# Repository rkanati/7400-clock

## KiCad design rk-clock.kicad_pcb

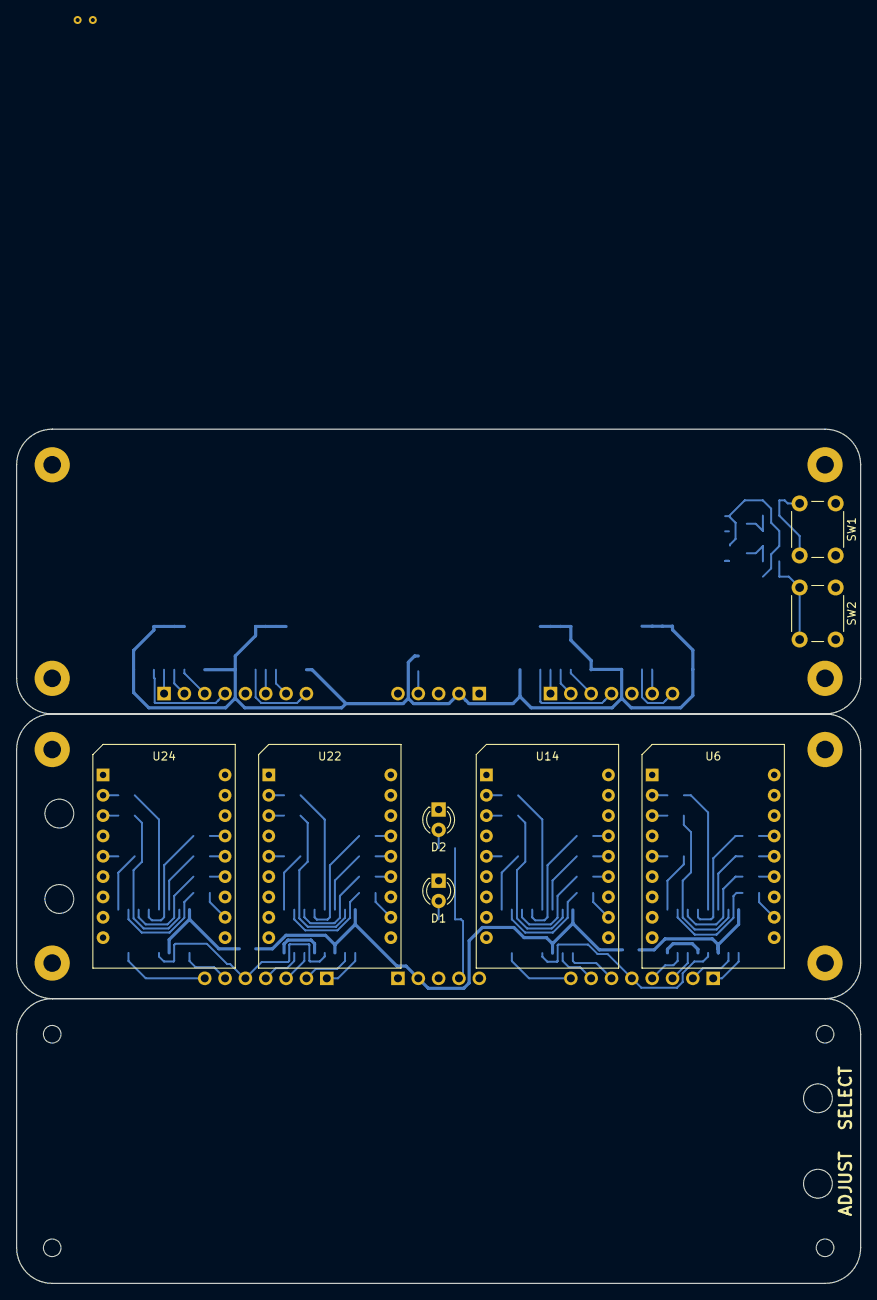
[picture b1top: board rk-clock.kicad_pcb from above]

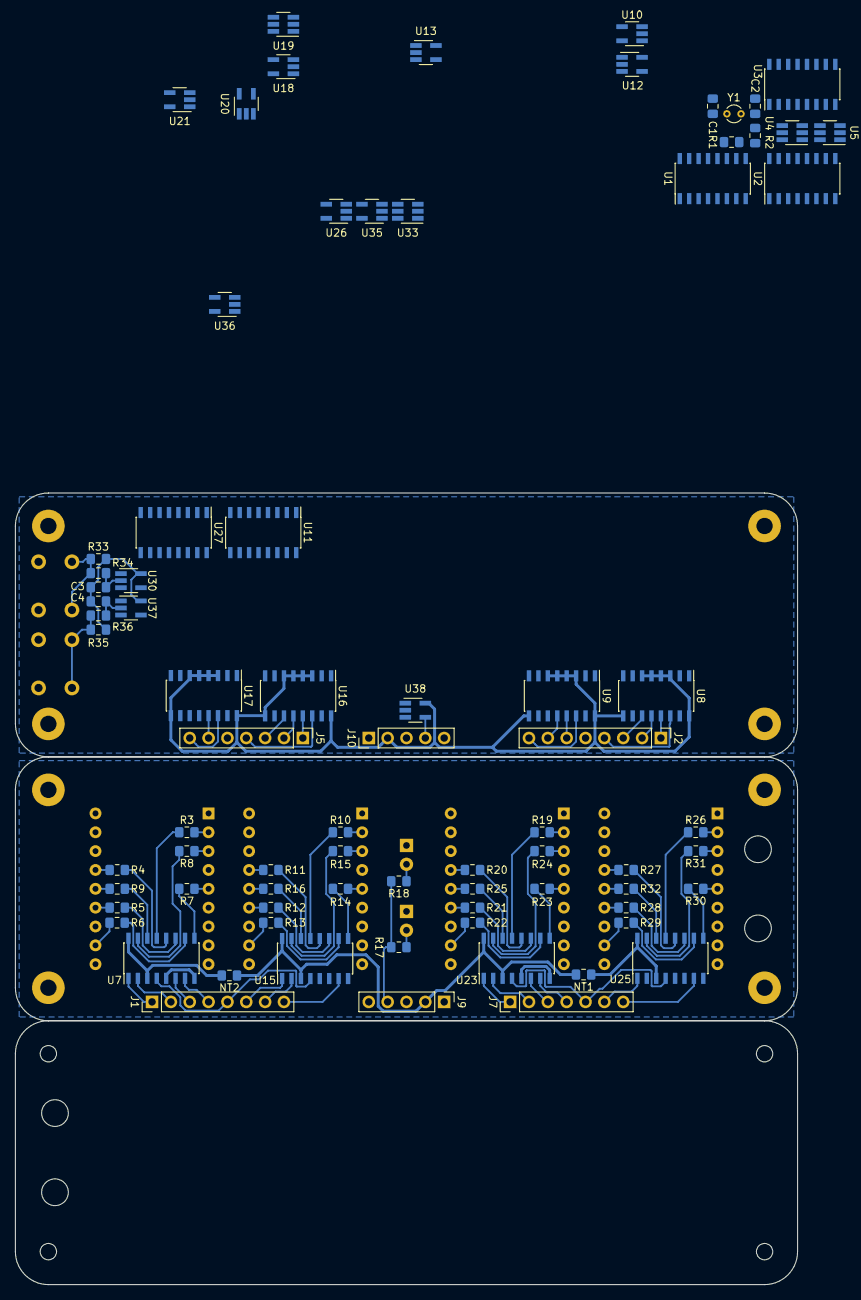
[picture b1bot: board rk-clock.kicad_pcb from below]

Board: 2 copper layers, 105.4 x 106.7 mm, 102 parts (78 on the bottom side), 132 nets.

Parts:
C1: 22p; C_0805_2012Metric_Pad1.15x1.40mm_HandSolder
C2: 100p; C_0805_2012Metric_Pad1.15x1.40mm_HandSolder
C3, C4: 1u; C_0805_2012Metric_Pad1.15x1.40mm_HandSolder
D1, D2: LED_Small; LED_D3.0mm
H1, H2, H3, H4, H9, H10, H11, H12: MountingHole_Pad; MountingHole_2.2mm_M2_Pad
H5, H6, H7, H8: MountingHole; MountingHole_2.2mm_M2
H13, H14, H15, H16: MountingHole; button-hole
J1: min_display; PinHeader_1x08_P2.54mm_Vertical
J2: min_control; PinHeader_1x08_P2.54mm_Vertical
J5: hour_control; PinHeader_1x07_P2.54mm_Vertical
J7: hour_display; PinHeader_1x07_P2.54mm_Vertical
J9: colon_display; PinHeader_1x05_P2.54mm_Vertical
J10: colon_control; PinHeader_1x05_P2.54mm_Vertical
NT1, NT2: Net-Tie_2; R_0805_2012Metric_Pad1.15x1.40mm_HandSolder
R1: 1M; R_0805_2012Metric_Pad1.15x1.40mm_HandSolder
R2: 2k2; R_0805_2012Metric_Pad1.15x1.40mm_HandSolder
R3, R4, R5, R6, R7, R8, R9, R10, R11, R12, R13, R14, R15, R16, R17, R18, R19, R20, R21, R22, R23, R24, R25, R26, R27, R28, R29, R30, R31, R32: 470; R_0805_2012Metric_Pad1.15x1.40mm_HandSolder
R33, R34, R35, R36: 47k; R_0805_2012Metric_Pad1.15x1.40mm_HandSolder
SW1: mode; SW_PUSH_6mm_H9.5mm
SW2: increase; SW_PUSH_6mm_H9.5mm
U1: '4060; SOIC-16_3.9x9.9mm_P1.27mm
U2, U3, U8, U9, U16, U17: '163; SOIC-16_3.9x9.9mm_P1.27mm
U4, U5, U33: '10; SOT-23-6_Handsoldering
U6, U14, U22, U24: LED-7Seg-18DIP; 7Seg-18DIP
U7, U15, U23, U25: '4511; SOIC-16_3.9x9.9mm_P1.27mm
U10, U13, U18, U26: '08; SOT-23-5_HandSoldering
U11: '158; SOIC-16_3.9x9.9mm_P1.27mm
U12, U21: '04; SOT-23-5_HandSoldering
U19: '11; SOT-23-6_Handsoldering
U20: '02; SOT-23-5_HandSoldering
U27: '175; SOIC-16_3.9x9.9mm_P1.27mm
U30, U37: '17; SOT-23-5_HandSoldering
U35, U36, U38: '32; SOT-23-5_HandSoldering
Y1: 32k768; Crystal_Round_D2.0mm_Vertical

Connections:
/2Hz_clk: U1.3, U2.2, U11.3
/DGND: D1.1, D2.1, H9.1, H10.1, H11.1, H12.1, J9.1, J9.3, J9.5, U6.4, U6.6, U6.9, U6.10, U6.12, U6.17, U7.5, U7.8, U14.4, U14.6, U14.9, U14.10, U14.12, U14.17, U15.5, U15.6, U15.8, U22.4, U22.6, U22.9, U22.10, U22.12, U22.17, U23.5, U23.8, U24.4, U24.6, U24.9, U24.10, U24.12, U24.17, U25.2, U25.5, U25.6, U25.8
/DVCC: J9.2, NT1.1, NT1.2, NT2.1, NT2.2, U7.3, U7.16, U15.3, U15.16, U23.3, U23.16, U25.3, U25.16
/colon_control: J10.4, U38.4
/count_clk: U8.2, U9.2, U11.4, U16.2, U17.2
/hour_bit0: J5.4, U16.14, U18.1, U19.1
/hour_bit1: J5.1, U16.13, U19.3
/hour_bit2: J5.2, U16.12
/hour_bit3: J5.3, U16.11, U18.2
/hour_en: U13.4, U16.7, U16.10
/min_bit0: J2.4, U8.14, U10.1
/min_bit1: J2.1, U8.13
/min_bit2: J2.2, U8.12
/min_bit3: J2.3, U8.11, U10.2
/min_en: U8.7, U8.10, U26.4
/tenhour_bit0: J5.7, U17.14
/tenhour_bit1: J5.6, U17.13, U19.6
/tenmin_bit0: J2.8, U9.14, U33.6
/tenmin_bit1: J2.6, U9.13
/tenmin_bit2: J2.7, U9.12, U33.1
/twosec_clk: U2.13, U4.1, U35.1, U36.1, U38.1
/~59_mins: U9.1, U11.14, U33.4
/~hour_blank: J5.5, U36.4
/~increase: U11.10, U37.4
/~min_blank: J2.5, U35.4
/~min_clk: U3.1, U5.4, U11.2
/~run: U11.1, U27.2, U38.2
/~set_hours: U11.13, U27.11, U36.2
/~set_mins: U11.6, U27.6, U35.2
GND: C1.2, C2.2, H1.1, H2.1, H3.1, H4.1, J10.1, J10.3, J10.5, SW1.1, SW2.1, U1.8, U1.12, U2.3, U2.4, U2.5, U2.6, U2.8, U3.3, U3.4, U3.5, U3.6, U3.8, U4.2, U5.2, U8.8, U9.8, U10.3, U11.5, U11.8, U11.11, U11.15, U12.3, U13.3, U16.8, U17.8, U18.3, U19.2, U20.3, U21.3, U26.3, U27.8, U30.3, U33.2, U35.3, U36.3, U37.3, U38.3
unnamed: C1.1, R1.2, U1.11, Y1.2
unnamed: C2.1, R2.2, Y1.1
unnamed: C3.2, R34.1, U30.2
unnamed: C4.2, R36.1, U37.2
unnamed: D1.2, R17.1
unnamed: D2.2, R18.1
unnamed: J1.1, U7.1
unnamed: J1.2, U7.2
unnamed: J1.3, U7.6
unnamed: J1.4, U7.7
unnamed: J1.5, U7.4, U15.4
unnamed: J1.6, U15.1
unnamed: J1.7, U15.2
unnamed: J1.8, U15.7
unnamed: J7.1, U23.1
unnamed: J7.2, U23.2
unnamed: J7.3, U23.6
unnamed: J7.4, U23.7
unnamed: J7.5, U23.4, U25.4
unnamed: J7.6, U25.1
unnamed: J7.7, U25.7
unnamed: J9.4, R17.2, R18.2
unnamed: R1.1, R2.1, U1.10
unnamed: R3.1, U6.2
unnamed: R3.2, U7.13
unnamed: R4.1, U6.15
unnamed: R4.2, U7.12
unnamed: R5.1, U6.13
unnamed: R5.2, U7.11
unnamed: R6.1, U6.11
unnamed: R6.2, U7.10
unnamed: R7.1, U6.5
unnamed: R7.2, U7.9
unnamed: R8.1, U6.3
unnamed: R8.2, U7.15
unnamed: R9.1, U6.14
unnamed: R9.2, U7.14
unnamed: R10.1, U14.2
unnamed: R10.2, U15.13
unnamed: R11.1, U14.15
unnamed: R11.2, U15.12
unnamed: R12.1, U14.13
unnamed: R12.2, U15.11
unnamed: R13.1, U14.11
unnamed: R13.2, U15.10
unnamed: R14.1, U14.5
unnamed: R14.2, U15.9
unnamed: R15.1, U14.3
unnamed: R15.2, U15.15
unnamed: R16.1, U14.14
unnamed: R16.2, U15.14
unnamed: R19.1, U22.2
unnamed: R19.2, U23.13
unnamed: R20.1, U22.15
unnamed: R20.2, U23.12
unnamed: R21.1, U22.13
unnamed: R21.2, U23.11
unnamed: R22.1, U22.11
unnamed: R22.2, U23.10
unnamed: R23.1, U22.5
unnamed: R23.2, U23.9
unnamed: R24.1, U22.3
unnamed: R24.2, U23.15
unnamed: R25.1, U22.14
unnamed: R25.2, U23.14
unnamed: R26.1, U24.2
unnamed: R26.2, U25.13
unnamed: R27.1, U24.15
unnamed: R27.2, U25.12
unnamed: R28.1, U24.13
unnamed: R28.2, U25.11
unnamed: R29.1, U24.11
unnamed: R29.2, U25.10
unnamed: R30.1, U24.5
unnamed: R30.2, U25.9
unnamed: R31.1, U24.3
unnamed: R31.2, U25.15
unnamed: R32.1, U24.14
unnamed: R32.2, U25.14
unnamed: R33.2, R34.2, SW1.2
unnamed: R35.2, R36.2, SW2.2
unnamed: U2.1, U3.2, U4.4
unnamed: U2.12, U4.3
unnamed: U2.14, U4.6
unnamed: U3.11, U5.3
unnamed: U3.12, U5.1
unnamed: U3.13, U5.6
unnamed: U9.7, U9.10, U10.4, U12.2, U33.3
unnamed: U11.7, U26.1
unnamed: U11.9, U13.2, U26.2
unnamed: U11.12, U13.1
unnamed: U8.1, U12.4
unnamed: U16.1, U20.4
unnamed: U17.1, U21.4
unnamed: U17.7, U17.10, U18.4, U20.2
unnamed: U19.4, U20.1, U21.2
unnamed: U27.1, U27.14
unnamed: U27.3, U27.5
unnamed: U27.9, U30.4
unnamed: U27.10, U27.13
unnamed: U27.7, U27.12
VCC: C3.1, C4.1, J10.2, R33.1, R35.1, U1.16, U2.7, U2.9, U2.10, U2.16, U3.7, U3.9, U3.10, U3.16, U4.5, U5.5, U8.3, U8.4, U8.5, U8.6, U8.9, U8.16, U9.3, U9.4, U9.5, U9.6, U9.9, U9.16, U10.5, U11.16, U12.5, U13.5, U16.3, U16.4, U16.5, U16.6, U16.9, U16.16, U17.3, U17.4, U17.5, U17.6, U17.9, U17.16, U18.5, U19.5, U20.5, U21.5, U26.5, U27.4, U27.16, U30.5, U33.5, U35.5, U36.5, U37.5, U38.5

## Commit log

2018-11-23 a few changes, some routing
